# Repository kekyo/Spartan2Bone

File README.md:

# Spartan2Bone

## What is this?

* This is prototyping board for Xilinx Spartan-II FPGA processor.
* These circuit mostly simple and easy usage, exclude any test devices.

## Features

* This board include features:
  * [Xilinx XC2S30 Spartan-II FPGA processor](https://www.xilinx.com/support/documentation/data_sheets/ds001.pdf)
  * [Xilinx XCF01S 1Mbit configuration flash ROM](https://www.xilinx.com/support/documentation/user_guides/ug161.pdf)
  * I/O header (IO[1..28], I_GCK[0..3], D[0..7], IRDY[1..2], TRDY[1..2], /WRITE, /CS, BUSY, INIT)
  * JTAG header
  * Mode jumper
  * 3.3V regulator and power configuration jumper

## Why Spartan-II now?

* Xilinx Spartan-II FPGA family already deprecated, these processors too old. But Spartan-II has "3.3V operation and 5V torelant I/Os."
* That means, easy usage for "Prototyping by breadboard or likely environments."
* We can get Spartan-II some market (ex: DigiKey). (2017 May)
* Another fit usages, we can use Xilinx XC95 CPLD series. This processors too old and NOT deprecated, but too few macro cells/registers. If you are interesting XC95, [try to my project PGA44DIP44](https://github.com/kekyo/PGA44DIP44).

TODO:

## Pre render output

## How to create Spartan2Bone

* Order and get Spartan2Bone PCB.

* Order and get required parts (TODO: parts list)

* Solder Spartan-II
  * Caution!! You must looks direction for Spartan-II! If you missed, repair too hard.

* Solder configuration flash ROM
  * Caution direction too.

* Cleaning by Flux remover.

* Solder other parts.

## Sample codes

### LedBrink

* [Sample for simple LED brink code. (Require Xilinx ISE 10.1)](LedBrink/)

### FizzBuzz

* [Sample for FizzBuzz by VerilogHDL. Output by 7seg LED and two Fizz-Buzz LEDs. (Require Xilinx ISE 10.1)](FizzBuzz/)

## LICENSE

* Schematic, artwork and documents: [Under CC BY-NC-SA 4.0](https://creativecommons.org/licenses/by-nc-sa/4.0/)
* Code: [Apache V2](https://www.apache.org/licenses/LICENSE-2.0)

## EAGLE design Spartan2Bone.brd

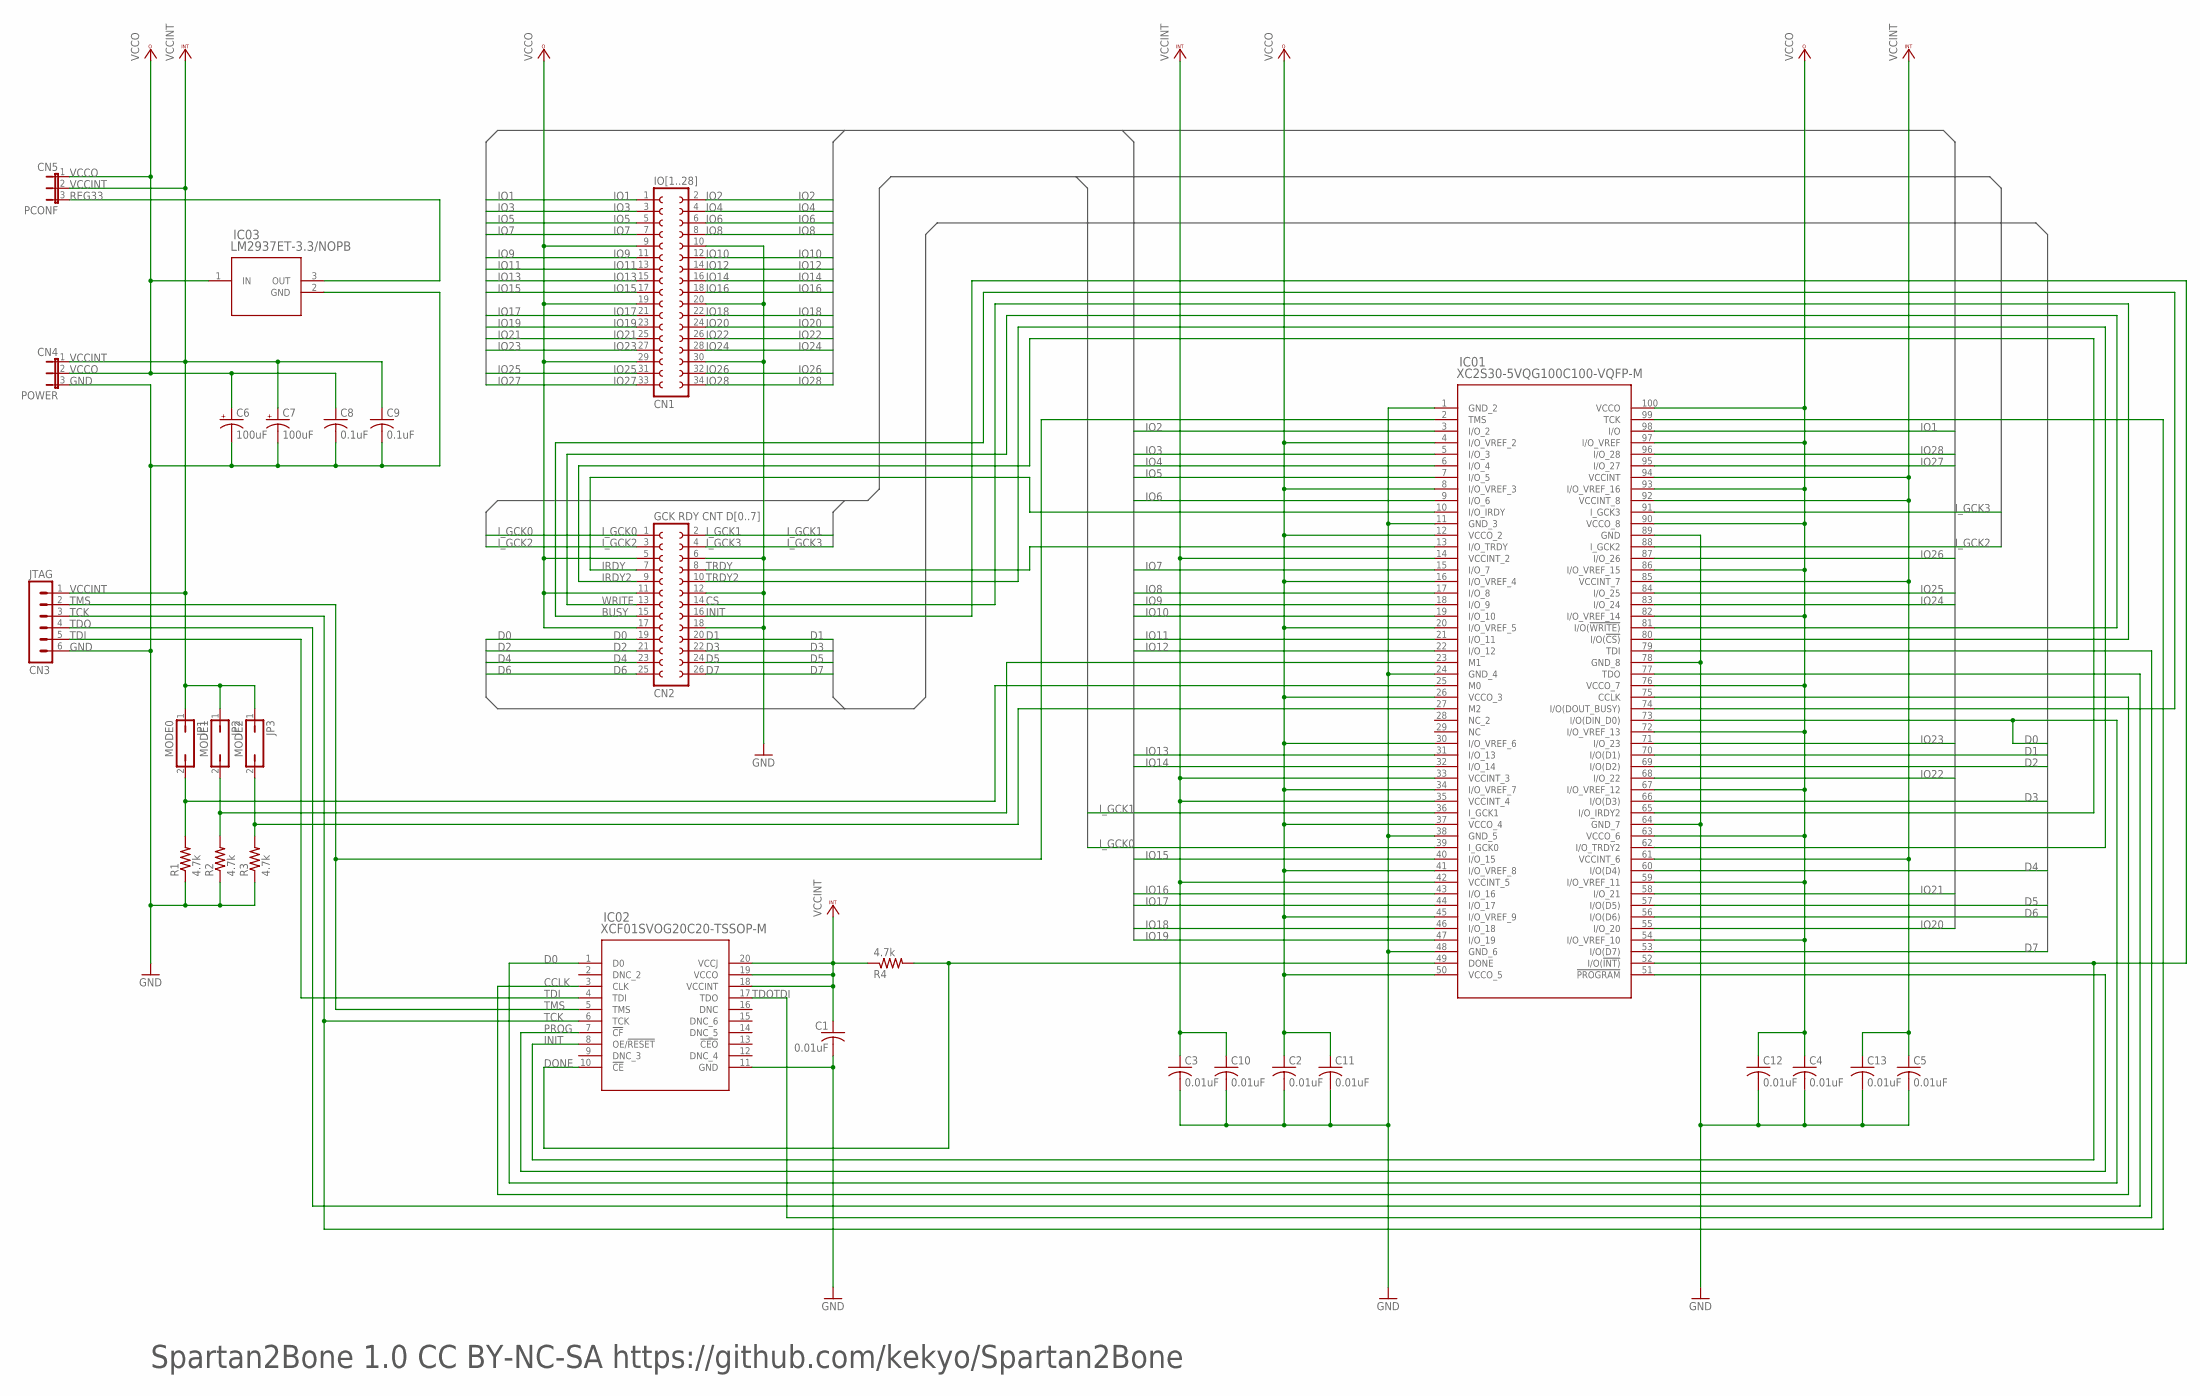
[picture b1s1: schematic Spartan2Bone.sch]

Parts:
C1, C2, C3, C4, C5, C10, C11, C12, C13: 0.01uF; C050-024X044
C6, C7: 100uF; E2,5-5
C8, C9: 0.1uF; C050-024X044
CN1: IO[1..28]; FE17-2
CN2: GCK RDY CNT D[0..7]; FE13-2
CN3: JTAG; MA06-1
CN4: POWER; JP2
CN5: PCONF; JP2
IC01: XC2S30-5VQG100C100-VQFP-M; 100-VQFP-M
IC02: XCF01SVOG20C20-TSSOP-M; 20-TSSOP-M
IC03: LM2937ET-3.3/NOPB; T03B
JP1: MODE0; JP1
JP2: MODE1; JP1
JP3: MODE2; JP1
R1, R2, R3, R4: 4.7k; 0204/5

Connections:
BUSY: CN2.15, IC01.74 (I/O(DOUT_BUSY))
CCLK: IC01.75 (CCLK), IC02.3 (CLK)
CS: CN2.14, IC01.80 (I/O(!CS))
D0: CN2.19, IC01.73 (I/O(DIN_D0)), IC02.1 (D0)
D1: CN2.20, IC01.70 (I/O(D1))
D2: CN2.21, IC01.69 (I/O(D2))
D3: CN2.22, IC01.66 (I/O(D3))
D4: CN2.23, IC01.60 (I/O(D4))
D5: CN2.24, IC01.57 (I/O(D5))
D6: CN2.25, IC01.56 (I/O(D6))
D7: CN2.26, IC01.53 (I/O(D7))
DONE: IC01.49 (DONE), IC02.10 (!CE), R4.2
GND: C1.2, C2.2, C3.2, C4.2, C5.2, C6.-, C7.-, C8.2, C9.2, C10.2, C11.2, C12.2, C13.2, CN1.10, CN1.20, CN1.30, CN2.6, CN2.12, CN2.18, CN3.6, CN4.3, IC01.1 (GND_2), IC01.11 (GND_3), IC01.24 (GND_4), IC01.38 (GND_5), IC01.48 (GND_6), IC01.64 (GND_7), IC01.78 (GND_8), IC01.89 (GND), IC02.11 (GND), IC03.2 (GND), R1.1, R2.1, R3.1
INIT: CN2.16, IC01.52 (I/O(!INT)), IC02.8 (OE/!RESET)
IO1: CN1.1, IC01.98 (I/O)
IO2: CN1.2, IC01.3 (I/O_2)
IO3: CN1.3, IC01.5 (I/O_3)
IO4: CN1.4, IC01.6 (I/O_4)
IO5: CN1.5, IC01.7 (I/O_5)
IO6: CN1.6, IC01.9 (I/O_6)
IO7: CN1.7, IC01.15 (I/O_7)
IO8: CN1.8, IC01.17 (I/O_8)
IO9: CN1.11, IC01.18 (I/O_9)
IO10: CN1.12, IC01.19 (I/O_10)
IO11: CN1.13, IC01.21 (I/O_11)
IO12: CN1.14, IC01.22 (I/O_12)
IO13: CN1.15, IC01.31 (I/O_13)
IO14: CN1.16, IC01.32 (I/O_14)
IO15: CN1.17, IC01.40 (I/O_15)
IO16: CN1.18, IC01.43 (I/O_16)
IO17: CN1.21, IC01.44 (I/O_17)
IO18: CN1.22, IC01.46 (I/O_18)
IO19: CN1.23, IC01.47 (I/O_19)
IO20: CN1.24, IC01.55 (I/O_20)
IO21: CN1.25, IC01.58 (I/O_21)
IO22: CN1.26, IC01.68 (I/O_22)
IO23: CN1.27, IC01.71 (I/O_23)
IO24: CN1.28, IC01.83 (I/O_24)
IO25: CN1.31, IC01.84 (I/O_25)
IO26: CN1.32, IC01.87 (I/O_26)
IO27: CN1.33, IC01.95 (I/O_27)
IO28: CN1.34, IC01.96 (I/O_28)
IRDY: CN2.7, IC01.10 (I/O_IRDY)
IRDY2: CN2.9, IC01.65 (I/O_IRDY2)
I_GCK0: CN2.1, IC01.39 (I_GCK0)
I_GCK1: CN2.2, IC01.36 (I_GCK1)
I_GCK2: CN2.3, IC01.88 (I_GCK2)
I_GCK3: CN2.4, IC01.91 (I_GCK3)
M0: IC01.25 (M0), JP1.2, R1.2
M1: IC01.23 (M1), JP2.2, R2.2
M2: IC01.27 (M2), JP3.2, R3.2
PROG: IC01.51 (!PROGRAM), IC02.7 (!CF)
REG33: CN5.3, IC03.3 (OUT)
TCK: CN3.3, IC01.99 (TCK), IC02.6 (TCK)
TDI: CN3.5, IC02.4 (TDI)
TDO: CN3.4, IC01.77 (TDO)
TDOTDI: IC01.79 (TDI), IC02.17 (TDO)
TMS: CN3.2, IC01.2 (TMS), IC02.5 (TMS)
TRDY: CN2.8, IC01.13 (I/O_TRDY)
TRDY2: CN2.10, IC01.62 (I/O_TRDY2)
VCCINT: C1.1, C3.1, C5.1, C7.+, C9.1, C10.1, C13.1, CN3.1, CN4.1, CN5.2, IC01.14 (VCCINT_2), IC01.33 (VCCINT_3), IC01.35 (VCCINT_4), IC01.42 (VCCINT_5), IC01.61 (VCCINT_6), IC01.85 (VCCINT_7), IC01.92 (VCCINT_8), IC01.94 (VCCINT), IC02.18 (VCCINT), IC02.19 (VCCO), IC02.20 (VCCJ), JP1.1, JP2.1, JP3.1, R4.1
VCCO: C2.1, C4.1, C6.+, C8.1, C11.1, C12.1, CN1.9, CN1.19, CN1.29, CN2.5, CN2.11, CN2.17, CN4.2, CN5.1, IC01.4 (I/O_VREF_2), IC01.8 (I/O_VREF_3), IC01.12 (VCCO_2), IC01.16 (I/O_VREF_4), IC01.20 (I/O_VREF_5), IC01.26 (VCCO_3), IC01.30 (I/O_VREF_6), IC01.34 (I/O_VREF_7), IC01.37 (VCCO_4), IC01.41 (I/O_VREF_8), IC01.45 (I/O_VREF_9), IC01.50 (VCCO_5), IC01.54 (I/O_VREF_10), IC01.59 (I/O_VREF_11), IC01.63 (VCCO_6), IC01.67 (I/O_VREF_12), IC01.72 (I/O_VREF_13), IC01.76 (VCCO_7), IC01.82 (I/O_VREF_14), IC01.86 (I/O_VREF_15), IC01.90 (VCCO_8), IC01.93 (I/O_VREF_16), IC01.97 (I/O_VREF), IC01.100 (VCCO), IC03.1 (IN)
WRITE: CN2.13, IC01.81 (I/O(!WRITE))

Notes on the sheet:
Spartan2Bone 1.0 CC BY-NC-SA https://github.com/kekyo/Spartan2Bone

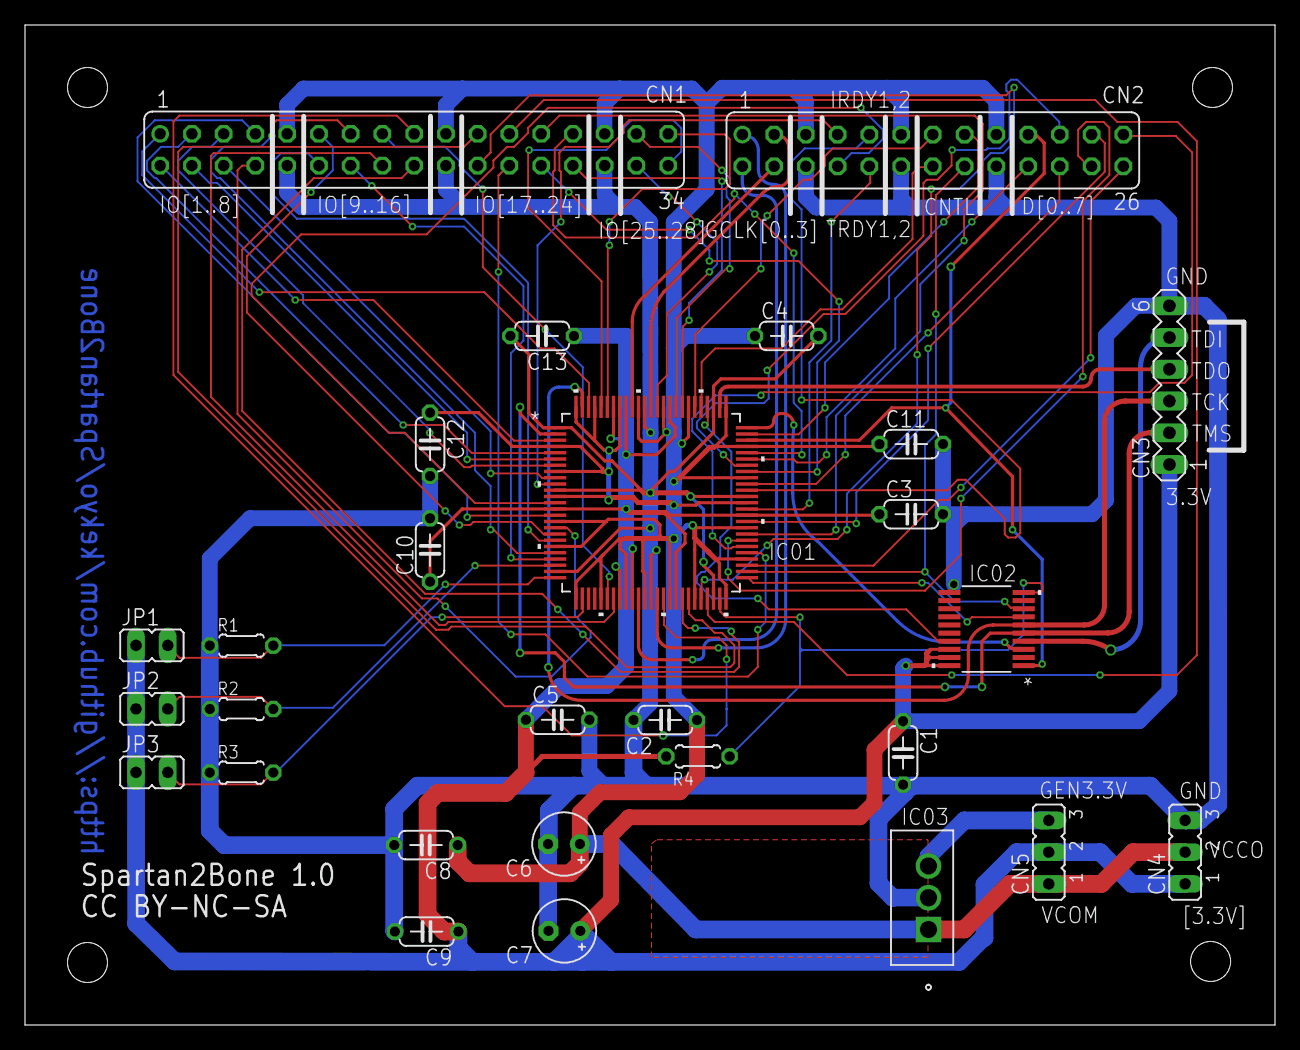
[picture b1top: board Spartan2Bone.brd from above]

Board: 2 copper layers, 100.0 x 80.0 mm, 28 parts (0 on the bottom side), 63 nets.

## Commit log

2017-03-30 Initial commit.
2017-03-30 Remove eagle project.
2017-03-30 Add image.
2017-03-30 Add readme.
2017-03-30 Bit changed.
2017-03-30 Add labels.
2017-03-30 Fixed ERC.
2017-03-31 Partial implement board design.
2017-03-31 Testing.
2017-04-01 First completion.
2017-04-01 Fixed board design.
2017-04-01 Add gerver files.
2017-04-22 EAGLE related files move to folder.
2017-05-02 First time LED brink tested.
2017-05-04 Add fizzbuzz sample.
2017-05-04 Update fizzbuzz mcs.
2017-05-05 * Add code header. * Add soldering images.
2017-05-05 Add sample video.
